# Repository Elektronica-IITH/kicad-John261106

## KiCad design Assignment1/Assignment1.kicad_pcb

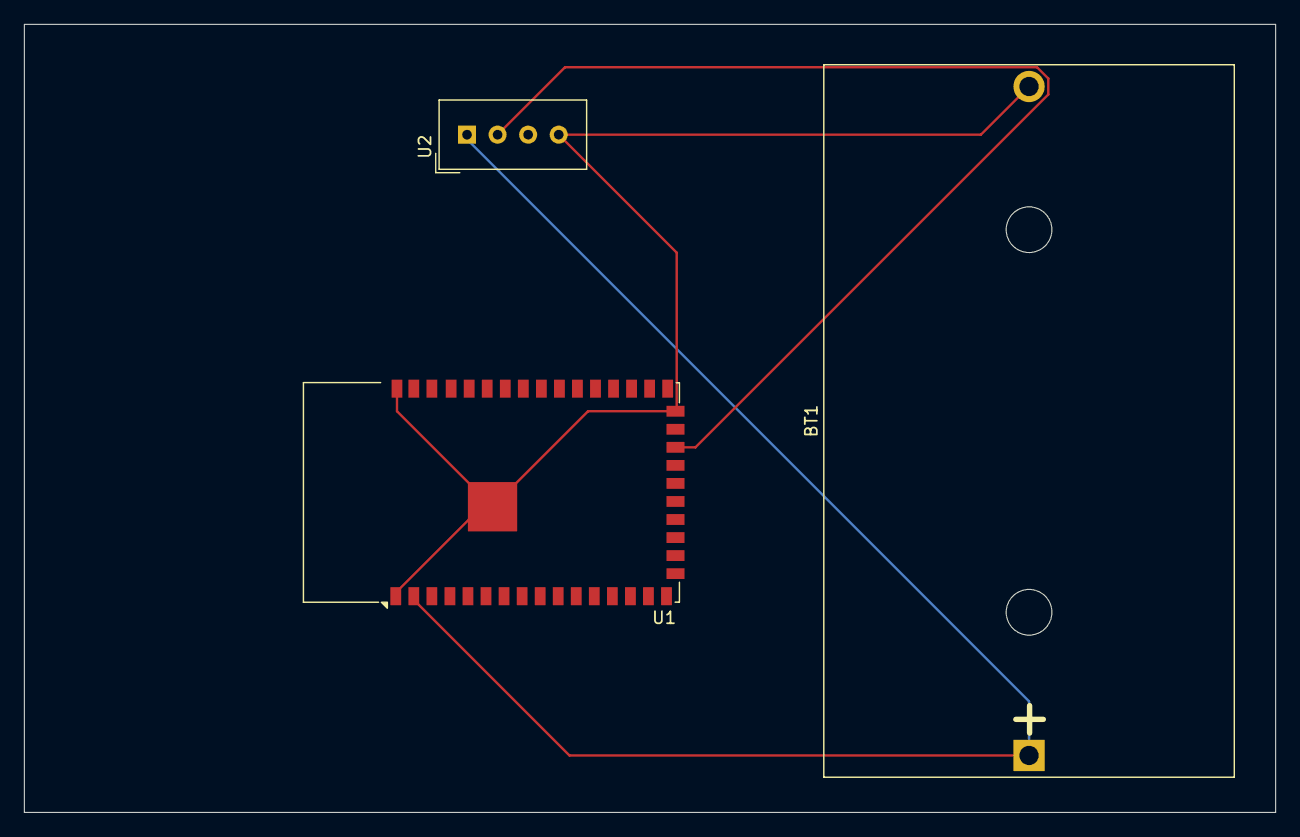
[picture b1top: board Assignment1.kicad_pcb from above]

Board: 2 copper layers, 104.0 x 65.5 mm, 3 parts (0 on the bottom side), 3 nets.

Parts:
BT1: Battery_Cell; BatteryHolder_Bulgin_BX0036_1xC
U1: ESP32-S2-WROVER
U2: DHT11; Aosong_DHT11_5.5x12.0_P2.54mm

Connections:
+3.3V: BT1.1 (+), U1.2 (3V3), U2.1 (VDD)
/DATA: U1.24 (IO21), U2.2 (DATA)
GND: BT1.2 (-), U1.1 (GND), U1.26 (GND), U1.42 (GND), U1.43 (GND), U2.4 (GND)

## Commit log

2025-03-29 ass1
2025-03-29 Automated PCB Check: Score 98/100
2025-04-05 ass2
